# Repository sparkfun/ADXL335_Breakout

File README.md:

SparkFun Triple Axis Accelerometer Breakout - ADXL335
======================

[*Triple Axis Accelerometer Breakout-ADXL335 (SEN-09269)*](https://www.sparkfun.com/products/9269)

This is a breakout board for teh 3-axis ADXL335 from Analog Devices. The sensor has a full sensing range of +- 3g and has an
analog output. 

Repository Contents
-------------------
* **/Hardware** - All Eagle design files (.brd, .sch)
* **/Production** - Test bed files and production panel files

Documentation
--------------
* **[Accelerometer Basics](https://learn.sparkfun.com/tutorials/accelerometer-basics)**

License Information
-------------------
The hardware is released under [Creative Commons ShareAlike 4.0 International](https://creativecommons.org/licenses/by-sa/4.0/).

Distributed as-is; no warranty is given.

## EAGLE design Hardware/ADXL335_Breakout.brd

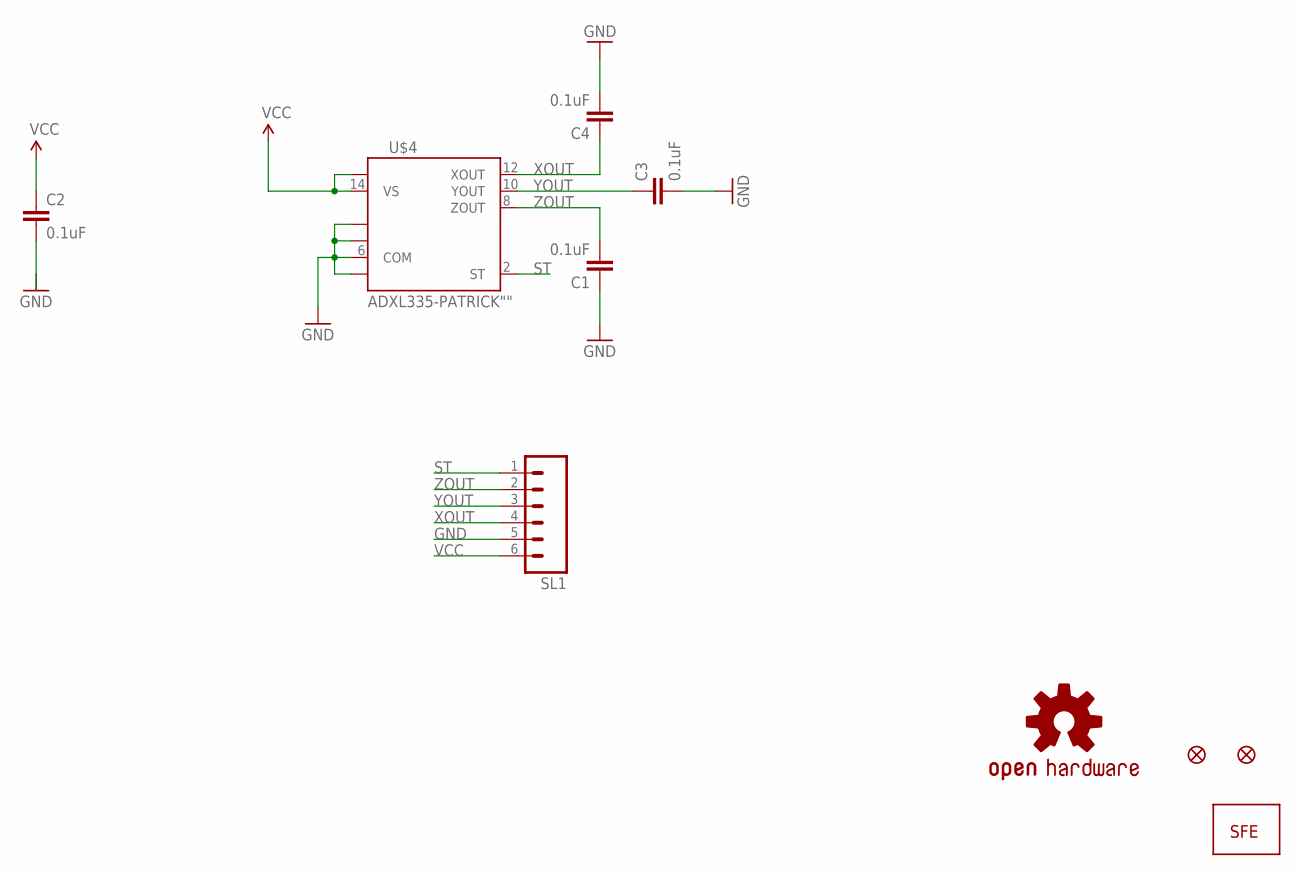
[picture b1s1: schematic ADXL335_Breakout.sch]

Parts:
C1, C2, C3, C4: 0.1uF; 0603-CAP
SL1: M06SIP; 1X06
U$1, U$3: FIDUCIAL1X2; FIDUCIAL-1X2
U$2: LOGO-SFE; SFE-NEW-WEBLOGO
U$4: ADXL335-PATRICK""; ADXL335-P
U$5: OSHW-LOGOS; OSHW-LOGO-S

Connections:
GND: C1.1, C2.2, C3.2, C4.2, SL1.5, U$4.3 (COM), U$4.5 (COM), U$4.6 (COM), U$4.7 (COM)
ST: SL1.1, U$4.2 (ST)
VCC: C2.1, SL1.6, U$4.14 (VS), U$4.15 (VS)
XOUT: C4.1, SL1.4, U$4.12 (XOUT)
YOUT: C3.1, SL1.3, U$4.10 (YOUT)
ZOUT: C1.2, SL1.2, U$4.8 (ZOUT)

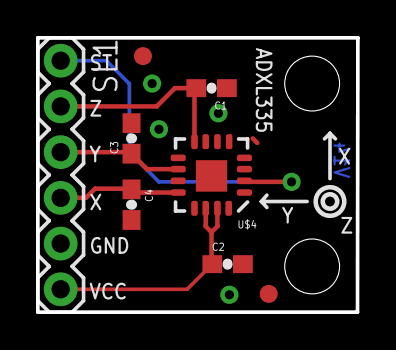
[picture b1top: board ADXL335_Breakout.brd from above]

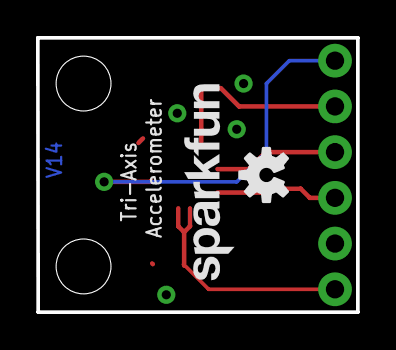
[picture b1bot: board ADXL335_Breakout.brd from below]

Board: 2 copper layers, 17.8 x 15.2 mm, 12 parts (2 on the bottom side), 6 nets.

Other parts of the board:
U$6, U$7: STAND-OFF-TIGHT
U$8: SFE_LOGO_NAME_.1

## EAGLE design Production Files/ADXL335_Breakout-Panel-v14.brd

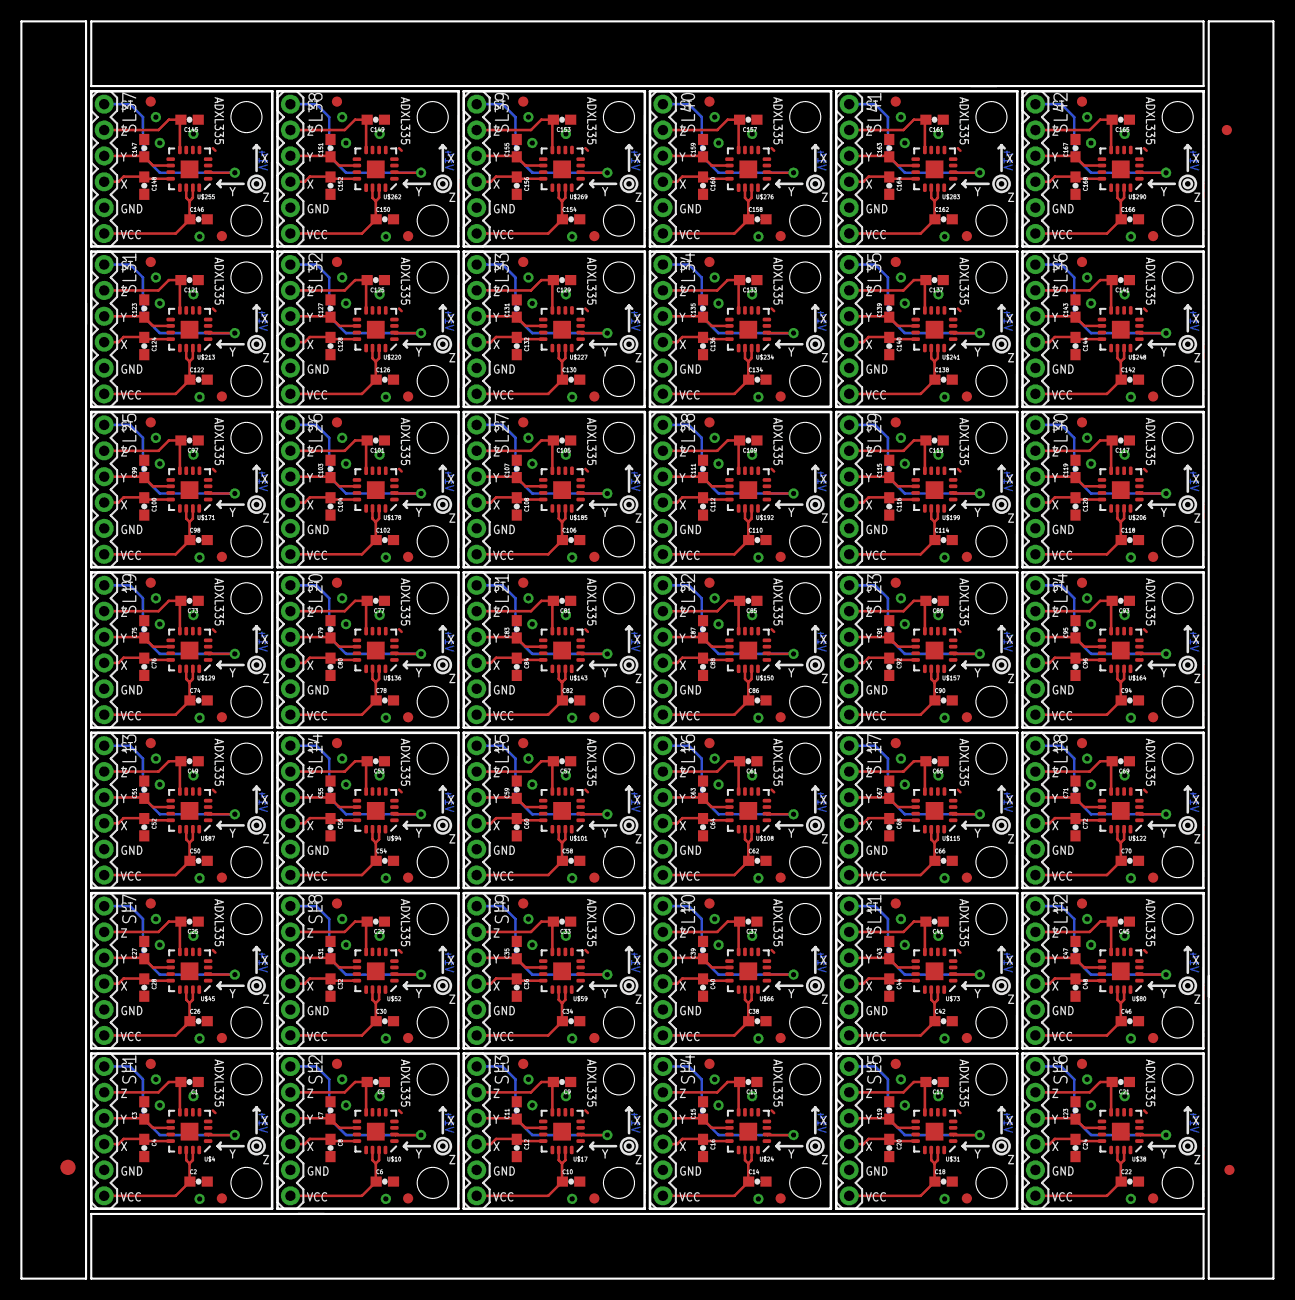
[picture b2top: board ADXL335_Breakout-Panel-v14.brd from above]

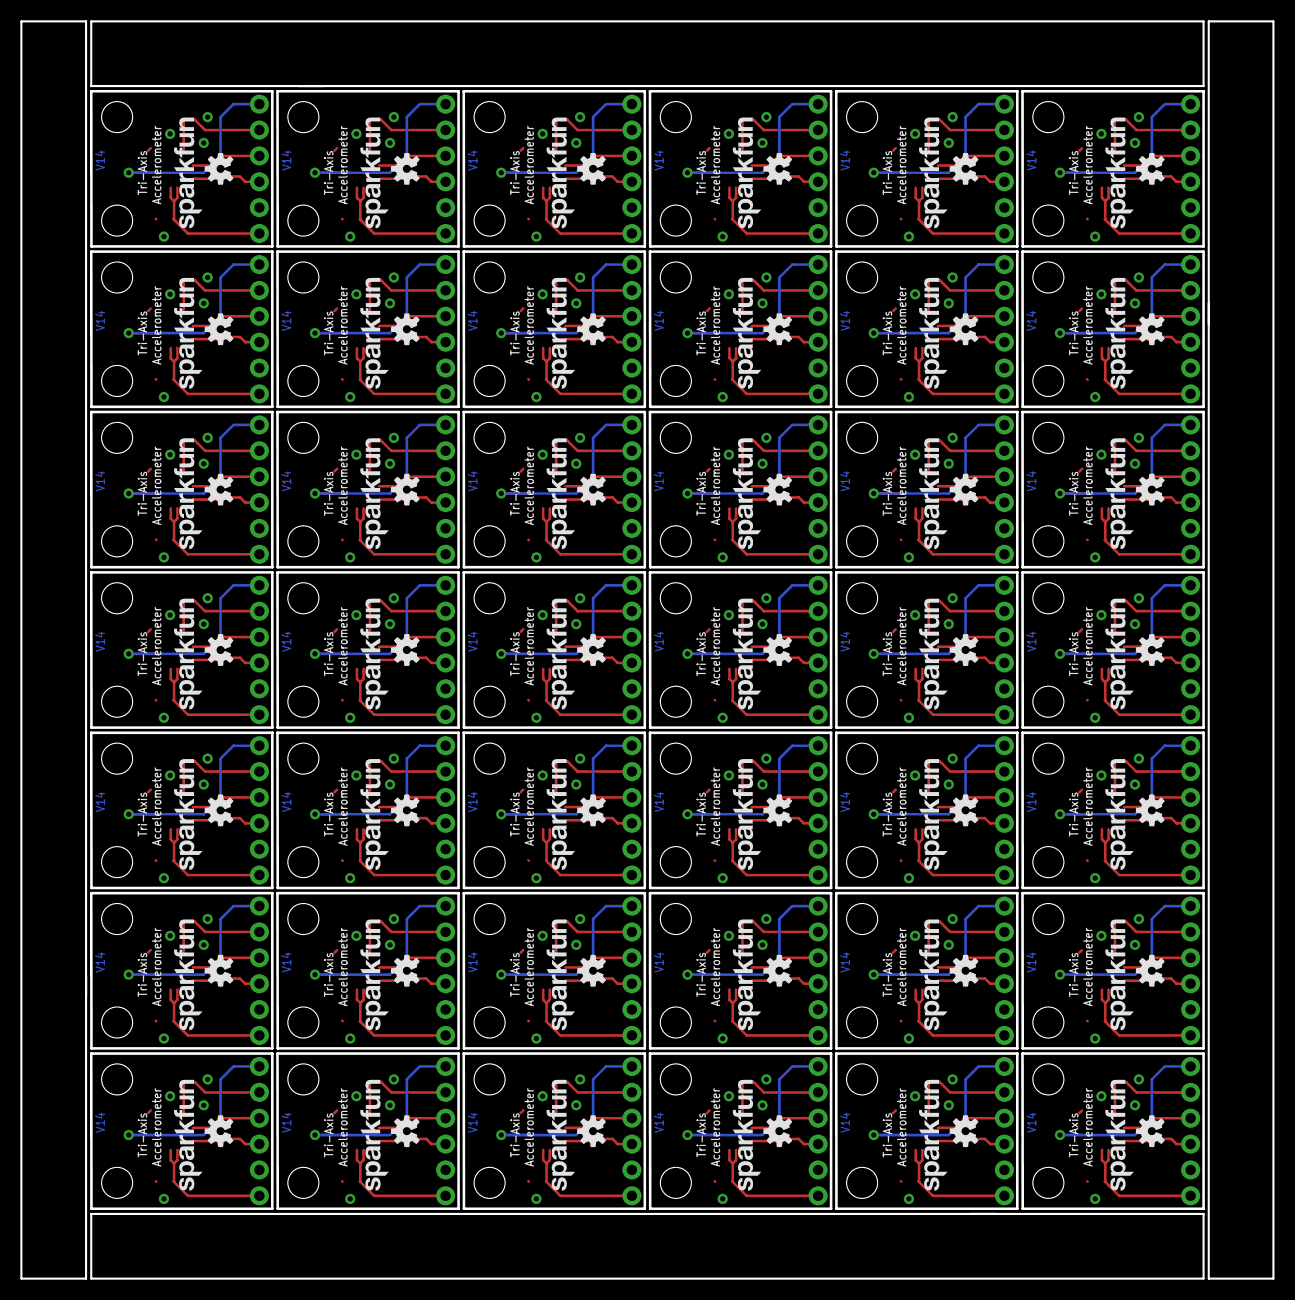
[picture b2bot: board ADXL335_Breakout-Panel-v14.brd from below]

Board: 2 copper layers, 122.9 x 123.4 mm, 507 parts (84 on the bottom side), 252 nets.

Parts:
C1, C2, C3, C4, C5, C6, C7, C8, C9, C10, C11, C12, C13, C14, C15, C16, C17, C18, C19, C20, C21, C22, C23, C24, C25, C26, C27, C28, C29, C30, C31, C32, C33, C34, C35, C36, C37, C38, C39, C40, C41, C42, C43, C44, C45, C46, C47, C48, C49, C50, C51, C52, C53, C54, C55, C56, C57, C58, C59, C60, C61, C62, C63, C64, C65, C66, C67, C68, C69, C70, C71, C72, C73, C74, C75, C76, C77, C78, C79, C80, C81, C82, C83, C84, C85, C86, C87, C88, C89, C90, C91, C92, C93, C94, C95, C96, C97, C98, C99, C100, C101, C102, C103, C104, C105, C106, C107, C108, C109, C110, C111, C112, C113, C114, C115, C116, C117, C118, C119, C120, C121, C122, C123, C124, C125, C126, C127, C128, C129, C130, C131, C132, C133, C134, C135, C136, C137, C138, C139, C140, C141, C142, C143, C144, C145, C146, C147, C148, C149, C150, C151, C152, C153, C154, C155, C156, C157, C158, C159, C160, C161, C162, C163, C164, C165, C166, C167, C168: 0.1uF; 0603-CAP
E$1: FIDUCIAL-1.5X3
E$4, E$5: FIDUCIAL-1X2
SL1, SL2, SL3, SL4, SL5, SL6, SL7, SL8, SL9, SL10, SL11, SL12, SL13, SL14, SL15, SL16, SL17, SL18, SL19, SL20, SL21, SL22, SL23, SL24, SL25, SL26, SL27, SL28, SL29, SL30, SL31, SL32, SL33, SL34, SL35, SL36, SL37, SL38, SL39, SL40, SL41, SL42: 1X06
U$1, U$2, U$3, U$9, U$15, U$16, U$22, U$23, U$29, U$30, U$36, U$37, U$43, U$44, U$50, U$51, U$57, U$58, U$64, U$65, U$71, U$72, U$78, U$79, U$85, U$86, U$92, U$93, U$99, U$100, U$106, U$107, U$113, U$114, U$120, U$121, U$127, U$128, U$134, U$135, U$141, U$142, U$148, U$149, U$155, U$156, U$162, U$163, U$169, U$170, U$176, U$177, U$183, U$184, U$190, U$191, U$197, U$198, U$204, U$205, U$211, U$212, U$218, U$219, U$225, U$226, U$232, U$233, U$239, U$240, U$246, U$247, U$253, U$254, U$260, U$261, U$267, U$268, U$274, U$275, U$281, U$282, U$288, U$289: FIDUCIAL1X2; FIDUCIAL-1X2
U$4, U$10, U$17, U$24, U$31, U$38, U$45, U$52, U$59, U$66, U$73, U$80, U$87, U$94, U$101, U$108, U$115, U$122, U$129, U$136, U$143, U$150, U$157, U$164, U$171, U$178, U$185, U$192, U$199, U$206, U$213, U$220, U$227, U$234, U$241, U$248, U$255, U$262, U$269, U$276, U$283, U$290: ADXL335-PATRICK""; ADXL335-P
U$5, U$13, U$20, U$27, U$34, U$41, U$48, U$55, U$62, U$69, U$76, U$83, U$90, U$97, U$104, U$111, U$118, U$125, U$132, U$139, U$146, U$153, U$160, U$167, U$174, U$181, U$188, U$195, U$202, U$209, U$216, U$223, U$230, U$237, U$244, U$251, U$258, U$265, U$272, U$279, U$286, U$293: OSHW-LOGO-S
U$6, U$7, U$11, U$12, U$18, U$19, U$25, U$26, U$32, U$33, U$39, U$40, U$46, U$47, U$53, U$54, U$60, U$61, U$67, U$68, U$74, U$75, U$81, U$82, U$88, U$89, U$95, U$96, U$102, U$103, U$109, U$110, U$116, U$117, U$123, U$124, U$130, U$131, U$137, U$138, U$144, U$145, U$151, U$152, U$158, U$159, U$165, U$166, U$172, U$173, U$179, U$180, U$186, U$187, U$193, U$194, U$200, U$201, U$207, U$208, U$214, U$215, U$221, U$222, U$228, U$229, U$235, U$236, U$242, U$243, U$249, U$250, U$256, U$257, U$263, U$264, U$270, U$271, U$277, U$278, U$284, U$285, U$291, U$292: STAND-OFF-TIGHT
U$8, U$14, U$21, U$28, U$35, U$42, U$49, U$56, U$63, U$70, U$77, U$84, U$91, U$98, U$105, U$112, U$119, U$126, U$133, U$140, U$147, U$154, U$161, U$168, U$175, U$182, U$189, U$196, U$203, U$210, U$217, U$224, U$231, U$238, U$245, U$252, U$259, U$266, U$273, U$280, U$287, U$294: SFE_LOGO_NAME_.1

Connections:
GND: C1.1, C2.2, C3.2, C4.2, SL1.5, U$4.3, U$4.5, U$4.6, U$4.7
GND1: C5.1, C6.2, C7.2, C8.2, SL2.5, U$10.3, U$10.5, U$10.6, U$10.7
GND2: C9.1, C10.2, C11.2, C12.2, SL3.5, U$17.3, U$17.5, U$17.6, U$17.7
GND3: C13.1, C14.2, C15.2, C16.2, SL4.5, U$24.3, U$24.5, U$24.6, U$24.7
GND4: C17.1, C18.2, C19.2, C20.2, SL5.5, U$31.3, U$31.5, U$31.6, U$31.7
GND5: C21.1, C22.2, C23.2, C24.2, SL6.5, U$38.3, U$38.5, U$38.6, U$38.7
GND6: C25.1, C26.2, C27.2, C28.2, SL7.5, U$45.3, U$45.5, U$45.6, U$45.7
GND7: C29.1, C30.2, C31.2, C32.2, SL8.5, U$52.3, U$52.5, U$52.6, U$52.7
GND8: C33.1, C34.2, C35.2, C36.2, SL9.5, U$59.3, U$59.5, U$59.6, U$59.7
GND9: C37.1, C38.2, C39.2, C40.2, SL10.5, U$66.3, U$66.5, U$66.6, U$66.7
GND10: C41.1, C42.2, C43.2, C44.2, SL11.5, U$73.3, U$73.5, U$73.6, U$73.7
GND11: C45.1, C46.2, C47.2, C48.2, SL12.5, U$80.3, U$80.5, U$80.6, U$80.7
GND12: C49.1, C50.2, C51.2, C52.2, SL13.5, U$87.3, U$87.5, U$87.6, U$87.7
GND13: C53.1, C54.2, C55.2, C56.2, SL14.5, U$94.3, U$94.5, U$94.6, U$94.7
GND14: C57.1, C58.2, C59.2, C60.2, SL15.5, U$101.3, U$101.5, U$101.6, U$101.7
GND15: C61.1, C62.2, C63.2, C64.2, SL16.5, U$108.3, U$108.5, U$108.6, U$108.7
GND16: C65.1, C66.2, C67.2, C68.2, SL17.5, U$115.3, U$115.5, U$115.6, U$115.7
GND17: C69.1, C70.2, C71.2, C72.2, SL18.5, U$122.3, U$122.5, U$122.6, U$122.7
GND18: C73.1, C74.2, C75.2, C76.2, SL19.5, U$129.3, U$129.5, U$129.6, U$129.7
GND19: C77.1, C78.2, C79.2, C80.2, SL20.5, U$136.3, U$136.5, U$136.6, U$136.7
GND20: C81.1, C82.2, C83.2, C84.2, SL21.5, U$143.3, U$143.5, U$143.6, U$143.7
GND21: C85.1, C86.2, C87.2, C88.2, SL22.5, U$150.3, U$150.5, U$150.6, U$150.7
GND22: C89.1, C90.2, C91.2, C92.2, SL23.5, U$157.3, U$157.5, U$157.6, U$157.7
GND23: C93.1, C94.2, C95.2, C96.2, SL24.5, U$164.3, U$164.5, U$164.6, U$164.7
GND24: C97.1, C98.2, C99.2, C100.2, SL25.5, U$171.3, U$171.5, U$171.6, U$171.7
GND25: C101.1, C102.2, C103.2, C104.2, SL26.5, U$178.3, U$178.5, U$178.6, U$178.7
GND26: C105.1, C106.2, C107.2, C108.2, SL27.5, U$185.3, U$185.5, U$185.6, U$185.7
GND27: C109.1, C110.2, C111.2, C112.2, SL28.5, U$192.3, U$192.5, U$192.6, U$192.7
GND28: C113.1, C114.2, C115.2, C116.2, SL29.5, U$199.3, U$199.5, U$199.6, U$199.7
GND29: C117.1, C118.2, C119.2, C120.2, SL30.5, U$206.3, U$206.5, U$206.6, U$206.7
GND30: C121.1, C122.2, C123.2, C124.2, SL31.5, U$213.3, U$213.5, U$213.6, U$213.7
GND31: C125.1, C126.2, C127.2, C128.2, SL32.5, U$220.3, U$220.5, U$220.6, U$220.7
GND32: C129.1, C130.2, C131.2, C132.2, SL33.5, U$227.3, U$227.5, U$227.6, U$227.7
GND33: C133.1, C134.2, C135.2, C136.2, SL34.5, U$234.3, U$234.5, U$234.6, U$234.7
GND34: C137.1, C138.2, C139.2, C140.2, SL35.5, U$241.3, U$241.5, U$241.6, U$241.7
GND35: C141.1, C142.2, C143.2, C144.2, SL36.5, U$248.3, U$248.5, U$248.6, U$248.7
GND36: C145.1, C146.2, C147.2, C148.2, SL37.5, U$255.3, U$255.5, U$255.6, U$255.7
GND37: C149.1, C150.2, C151.2, C152.2, SL38.5, U$262.3, U$262.5, U$262.6, U$262.7
GND38: C153.1, C154.2, C155.2, C156.2, SL39.5, U$269.3, U$269.5, U$269.6, U$269.7
GND39: C157.1, C158.2, C159.2, C160.2, SL40.5, U$276.3, U$276.5, U$276.6, U$276.7
GND40: C161.1, C162.2, C163.2, C164.2, SL41.5, U$283.3, U$283.5, U$283.6, U$283.7
GND41: C165.1, C166.2, C167.2, C168.2, SL42.5, U$290.3, U$290.5, U$290.6, U$290.7
ST: SL1.1, U$4.2
ST1: SL2.1, U$10.2
ST2: SL3.1, U$17.2
ST3: SL4.1, U$24.2
ST4: SL5.1, U$31.2
ST5: SL6.1, U$38.2
ST6: SL7.1, U$45.2
ST7: SL8.1, U$52.2
ST8: SL9.1, U$59.2
ST9: SL10.1, U$66.2
ST10: SL11.1, U$73.2
ST11: SL12.1, U$80.2
ST12: SL13.1, U$87.2
ST13: SL14.1, U$94.2
ST14: SL15.1, U$101.2
ST15: SL16.1, U$108.2
ST16: SL17.1, U$115.2
ST17: SL18.1, U$122.2
ST18: SL19.1, U$129.2
ST19: SL20.1, U$136.2
ST20: SL21.1, U$143.2
ST21: SL22.1, U$150.2
ST22: SL23.1, U$157.2
ST23: SL24.1, U$164.2
ST24: SL25.1, U$171.2
ST25: SL26.1, U$178.2
ST26: SL27.1, U$185.2
ST27: SL28.1, U$192.2
ST28: SL29.1, U$199.2
ST29: SL30.1, U$206.2
ST30: SL31.1, U$213.2
ST31: SL32.1, U$220.2
ST32: SL33.1, U$227.2
ST33: SL34.1, U$234.2
ST34: SL35.1, U$241.2
ST35: SL36.1, U$248.2
ST36: SL37.1, U$255.2
ST37: SL38.1, U$262.2
ST38: SL39.1, U$269.2
ST39: SL40.1, U$276.2
ST40: SL41.1, U$283.2
ST41: SL42.1, U$290.2
VCC: C2.1, SL1.6, U$4.14, U$4.15
VCC1: C6.1, SL2.6, U$10.14, U$10.15
VCC2: C10.1, SL3.6, U$17.14, U$17.15
VCC3: C14.1, SL4.6, U$24.14, U$24.15
VCC4: C18.1, SL5.6, U$31.14, U$31.15
VCC5: C22.1, SL6.6, U$38.14, U$38.15
VCC6: C26.1, SL7.6, U$45.14, U$45.15
VCC7: C30.1, SL8.6, U$52.14, U$52.15
VCC8: C34.1, SL9.6, U$59.14, U$59.15
VCC9: C38.1, SL10.6, U$66.14, U$66.15
VCC10: C42.1, SL11.6, U$73.14, U$73.15
VCC11: C46.1, SL12.6, U$80.14, U$80.15
VCC12: C50.1, SL13.6, U$87.14, U$87.15
VCC13: C54.1, SL14.6, U$94.14, U$94.15
VCC14: C58.1, SL15.6, U$101.14, U$101.15
VCC15: C62.1, SL16.6, U$108.14, U$108.15
VCC16: C66.1, SL17.6, U$115.14, U$115.15
VCC17: C70.1, SL18.6, U$122.14, U$122.15
VCC18: C74.1, SL19.6, U$129.14, U$129.15
VCC19: C78.1, SL20.6, U$136.14, U$136.15
VCC20: C82.1, SL21.6, U$143.14, U$143.15
VCC21: C86.1, SL22.6, U$150.14, U$150.15
VCC22: C90.1, SL23.6, U$157.14, U$157.15
VCC23: C94.1, SL24.6, U$164.14, U$164.15
VCC24: C98.1, SL25.6, U$171.14, U$171.15
VCC25: C102.1, SL26.6, U$178.14, U$178.15
VCC26: C106.1, SL27.6, U$185.14, U$185.15
VCC27: C110.1, SL28.6, U$192.14, U$192.15
VCC28: C114.1, SL29.6, U$199.14, U$199.15
VCC29: C118.1, SL30.6, U$206.14, U$206.15
VCC30: C122.1, SL31.6, U$213.14, U$213.15
VCC31: C126.1, SL32.6, U$220.14, U$220.15
VCC32: C130.1, SL33.6, U$227.14, U$227.15
VCC33: C134.1, SL34.6, U$234.14, U$234.15
VCC34: C138.1, SL35.6, U$241.14, U$241.15
VCC35: C142.1, SL36.6, U$248.14, U$248.15
VCC36: C146.1, SL37.6, U$255.14, U$255.15
VCC37: C150.1, SL38.6, U$262.14, U$262.15
VCC38: C154.1, SL39.6, U$269.14, U$269.15
VCC39: C158.1, SL40.6, U$276.14, U$276.15
VCC40: C162.1, SL41.6, U$283.14, U$283.15
VCC41: C166.1, SL42.6, U$290.14, U$290.15
XOUT: C4.1, SL1.4, U$4.12
XOUT1: C8.1, SL2.4, U$10.12
XOUT2: C12.1, SL3.4, U$17.12
XOUT3: C16.1, SL4.4, U$24.12
XOUT4: C20.1, SL5.4, U$31.12
XOUT5: C24.1, SL6.4, U$38.12
XOUT6: C28.1, SL7.4, U$45.12
XOUT7: C32.1, SL8.4, U$52.12
XOUT8: C36.1, SL9.4, U$59.12
XOUT9: C40.1, SL10.4, U$66.12
XOUT10: C44.1, SL11.4, U$73.12
XOUT11: C48.1, SL12.4, U$80.12
XOUT12: C52.1, SL13.4, U$87.12
XOUT13: C56.1, SL14.4, U$94.12
XOUT14: C60.1, SL15.4, U$101.12
XOUT15: C64.1, SL16.4, U$108.12
XOUT16: C68.1, SL17.4, U$115.12
XOUT17: C72.1, SL18.4, U$122.12
XOUT18: C76.1, SL19.4, U$129.12
XOUT19: C80.1, SL20.4, U$136.12
XOUT20: C84.1, SL21.4, U$143.12
XOUT21: C88.1, SL22.4, U$150.12
XOUT22: C92.1, SL23.4, U$157.12
XOUT23: C96.1, SL24.4, U$164.12
XOUT24: C100.1, SL25.4, U$171.12
XOUT25: C104.1, SL26.4, U$178.12
XOUT26: C108.1, SL27.4, U$185.12
XOUT27: C112.1, SL28.4, U$192.12
XOUT28: C116.1, SL29.4, U$199.12
XOUT29: C120.1, SL30.4, U$206.12
XOUT30: C124.1, SL31.4, U$213.12
XOUT31: C128.1, SL32.4, U$220.12
XOUT32: C132.1, SL33.4, U$227.12
XOUT33: C136.1, SL34.4, U$234.12
XOUT34: C140.1, SL35.4, U$241.12
XOUT35: C144.1, SL36.4, U$248.12
XOUT36: C148.1, SL37.4, U$255.12
XOUT37: C152.1, SL38.4, U$262.12
XOUT38: C156.1, SL39.4, U$269.12
XOUT39: C160.1, SL40.4, U$276.12
XOUT40: C164.1, SL41.4, U$283.12
XOUT41: C168.1, SL42.4, U$290.12
YOUT: C3.1, SL1.3, U$4.10
YOUT1: C7.1, SL2.3, U$10.10
YOUT2: C11.1, SL3.3, U$17.10
YOUT3: C15.1, SL4.3, U$24.10
YOUT4: C19.1, SL5.3, U$31.10
YOUT5: C23.1, SL6.3, U$38.10
YOUT6: C27.1, SL7.3, U$45.10
YOUT7: C31.1, SL8.3, U$52.10
YOUT8: C35.1, SL9.3, U$59.10
YOUT9: C39.1, SL10.3, U$66.10
YOUT10: C43.1, SL11.3, U$73.10
YOUT11: C47.1, SL12.3, U$80.10
YOUT12: C51.1, SL13.3, U$87.10
YOUT13: C55.1, SL14.3, U$94.10
YOUT14: C59.1, SL15.3, U$101.10
YOUT15: C63.1, SL16.3, U$108.10
YOUT16: C67.1, SL17.3, U$115.10
YOUT17: C71.1, SL18.3, U$122.10
YOUT18: C75.1, SL19.3, U$129.10
YOUT19: C79.1, SL20.3, U$136.10
YOUT20: C83.1, SL21.3, U$143.10
YOUT21: C87.1, SL22.3, U$150.10
YOUT22: C91.1, SL23.3, U$157.10
YOUT23: C95.1, SL24.3, U$164.10
YOUT24: C99.1, SL25.3, U$171.10
YOUT25: C103.1, SL26.3, U$178.10
YOUT26: C107.1, SL27.3, U$185.10
YOUT27: C111.1, SL28.3, U$192.10
YOUT28: C115.1, SL29.3, U$199.10
YOUT29: C119.1, SL30.3, U$206.10
YOUT30: C123.1, SL31.3, U$213.10
YOUT31: C127.1, SL32.3, U$220.10
YOUT32: C131.1, SL33.3, U$227.10
YOUT33: C135.1, SL34.3, U$234.10
YOUT34: C139.1, SL35.3, U$241.10
YOUT35: C143.1, SL36.3, U$248.10
YOUT36: C147.1, SL37.3, U$255.10
YOUT37: C151.1, SL38.3, U$262.10
YOUT38: C155.1, SL39.3, U$269.10
YOUT39: C159.1, SL40.3, U$276.10
YOUT40: C163.1, SL41.3, U$283.10
YOUT41: C167.1, SL42.3, U$290.10
ZOUT: C1.2, SL1.2, U$4.8
ZOUT1: C5.2, SL2.2, U$10.8
ZOUT2: C9.2, SL3.2, U$17.8
ZOUT3: C13.2, SL4.2, U$24.8
ZOUT4: C17.2, SL5.2, U$31.8
ZOUT5: C21.2, SL6.2, U$38.8
ZOUT6: C25.2, SL7.2, U$45.8
ZOUT7: C29.2, SL8.2, U$52.8
ZOUT8: C33.2, SL9.2, U$59.8
ZOUT9: C37.2, SL10.2, U$66.8
ZOUT10: C41.2, SL11.2, U$73.8
ZOUT11: C45.2, SL12.2, U$80.8
ZOUT12: C49.2, SL13.2, U$87.8
ZOUT13: C53.2, SL14.2, U$94.8
ZOUT14: C57.2, SL15.2, U$101.8
ZOUT15: C61.2, SL16.2, U$108.8
ZOUT16: C65.2, SL17.2, U$115.8
ZOUT17: C69.2, SL18.2, U$122.8
ZOUT18: C73.2, SL19.2, U$129.8
ZOUT19: C77.2, SL20.2, U$136.8
ZOUT20: C81.2, SL21.2, U$143.8
ZOUT21: C85.2, SL22.2, U$150.8
ZOUT22: C89.2, SL23.2, U$157.8
ZOUT23: C93.2, SL24.2, U$164.8
ZOUT24: C97.2, SL25.2, U$171.8
ZOUT25: C101.2, SL26.2, U$178.8
ZOUT26: C105.2, SL27.2, U$185.8
ZOUT27: C109.2, SL28.2, U$192.8
ZOUT28: C113.2, SL29.2, U$199.8
ZOUT29: C117.2, SL30.2, U$206.8
ZOUT30: C121.2, SL31.2, U$213.8
ZOUT31: C125.2, SL32.2, U$220.8
ZOUT32: C129.2, SL33.2, U$227.8
ZOUT33: C133.2, SL34.2, U$234.8
ZOUT34: C137.2, SL35.2, U$241.8
ZOUT35: C141.2, SL36.2, U$248.8
ZOUT36: C145.2, SL37.2, U$255.8
ZOUT37: C149.2, SL38.2, U$262.8
ZOUT38: C153.2, SL39.2, U$269.8
ZOUT39: C157.2, SL40.2, U$276.8
ZOUT40: C161.2, SL41.2, U$283.8
ZOUT41: C165.2, SL42.2, U$290.8

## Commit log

2013-08-20 Initial Commit
    added v13 brd/sch
2013-09-20 Package Change, Switched to 0603
    Did a 1:1 footprint on the Adxl335, changed all 0402's to 0603, minor
    trace re-routing.
2013-09-20 T-Res change/ Removed Traces/Pour Dimension Change
    Added t restrict to a few pins for better solder flow, also removed
    traces on the ground for the bottom and top copper as it was
    unnecessary. Also made the top copper pour dimension match the bottom
    copper pour
2013-09-23 Rev Dimension/Silk Design and more
    A redo on the dimension of the PCB, Added a new axis to the silk,
    revised the bplace with new aesthetics. Also standoff holes were added.
2013-10-16 moved fiducials
2013-10-16 Minor pre-production fixes
    1.) Fixed an air-wire.
    2.) Changed all traces to same width.
2013-10-16 Created Panel
2014-02-06 Updating README

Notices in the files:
parts and their libraries:
SparkFun-Aesthetics: Licensing: CC v3.0 Share-Alike You are welcome to use this library for commercial purposes.
